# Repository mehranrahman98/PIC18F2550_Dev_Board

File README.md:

# PIC18F2550 Development Board
KiCAD PCB Design of PIC18F2550 development board. Similar to Arduino functionality.

## PCB

## Schematic

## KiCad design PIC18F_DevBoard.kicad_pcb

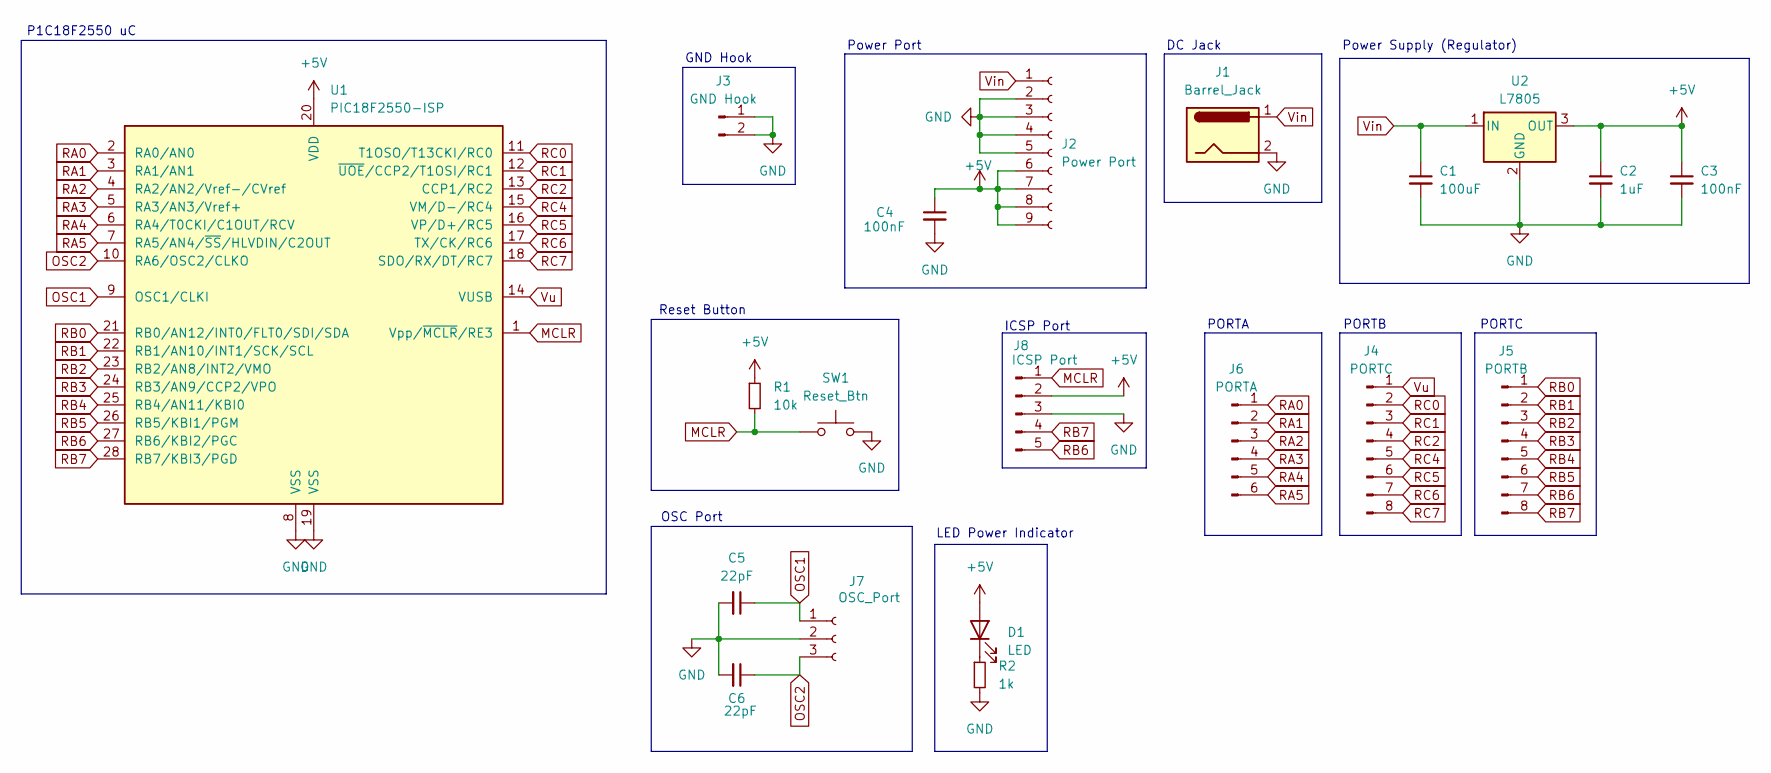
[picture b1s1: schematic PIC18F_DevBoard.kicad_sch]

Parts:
C1: 100uF; CP_Radial_D4.0mm_P2.00mm
C2: 1uF; CP_Radial_D4.0mm_P1.50mm
C3, C4: 100nF; C_Disc_D3.0mm_W1.6mm_P2.50mm
C5, C6: 22pF; C_Disc_D3.0mm_W1.6mm_P2.50mm
D1: LED; LED_D3.0mm
J1: Barrel_Jack; BarrelJack_Horizontal
J2: Power Port; PinSocket_1x09_P2.54mm_Vertical
J3: GND Hook; PinHeader_1x02_P2.54mm_Vertical
J4: PORTC; PinSocket_1x08_P2.54mm_Vertical
J5: PORTB; PinSocket_1x08_P2.54mm_Vertical
J6: PORTA; PinSocket_1x06_P2.54mm_Vertical
J7: OSC_Port; PinSocket_1x03_P2.54mm_Vertical
J8: ICSP Port; PinSocket_1x05_P2.54mm_Vertical
R1: 10k; R_Axial_DIN0204_L3.6mm_D1.6mm_P5.08mm_Horizontal
R2: 1k; R_Axial_DIN0204_L3.6mm_D1.6mm_P5.08mm_Horizontal
SW1: Reset_Btn; SW_PUSH_6mm
U1: PIC18F2550-ISP; DIP-28_W7.62mm
U2: L7805; TO-220-3_Horizontal_TabDown

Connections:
+5V: C2.1, C3.1, C4.1, D1.2 (A), J2.6, J2.7, J2.8, J2.9, J8.2, R1.1, U1.20 (VDD), U2.3 (OUT)
GND: C1.2, C2.2, C3.2, C4.2, C5.2, C6.2, J1.2, J2.2, J2.3, J2.4, J2.5, J3.1, J3.2, J7.2, J8.3, R2.2, SW1.2, U1.8 (VSS), U1.19 (VSS), U2.2 (GND)
MCLR: J8.1, R1.2, SW1.1, U1.1 (Vpp/~MCLR/RE3)
unnamed: D1.1 (K), R2.1
OSC1: C5.1, J7.1, U1.9 (OSC1/CLKI)
OSC2: C6.1, J7.3, U1.10 (RA6/OSC2/CLKO)
RA0: J6.1, U1.2 (RA0/AN0)
RA1: J6.2, U1.3 (RA1/AN1)
RA2: J6.3, U1.4 (RA2/AN2/Vref-/CVref)
RA3: J6.4, U1.5 (RA3/AN3/Vref+)
RA4: J6.5, U1.6 (RA4/T0CKI/C1OUT/RCV)
RA5: J6.6, U1.7 (RA5/AN4/~SS/HLVDIN/C2OUT)
RB0: J5.1, U1.21 (RB0/AN12/INT0/FLT0/SDI/SDA)
RB1: J5.2, U1.22 (RB1/AN10/INT1/SCK/SCL)
RB2: J5.3, U1.23 (RB2/AN8/INT2/VMO)
RB3: J5.4, U1.24 (RB3/AN9/CCP2/VPO)
RB4: J5.5, U1.25 (RB4/AN11/KBI0)
RB5: J5.6, U1.26 (RB5/KBI1/PGM)
RB6: J5.7, J8.5, U1.27 (RB6/KBI2/PGC)
RB7: J5.8, J8.4, U1.28 (RB7/KBI3/PGD)
RC0: J4.2, U1.11 (T1OSO/T13CKI/RC0)
RC1: J4.3, U1.12 (~UOE/CCP2/T1OSI/RC1)
RC2: J4.4, U1.13 (CCP1/RC2)
RC4: J4.5, U1.15 (VM/D-/RC4)
RC5: J4.6, U1.16 (VP/D+/RC5)
RC6: J4.7, U1.17 (TX/CK/RC6)
RC7: J4.8, U1.18 (SDO/RX/DT/RC7)
Vin: C1.1, J1.1, J2.1, U2.1 (IN)
Vu: J4.1, U1.14 (VUSB)

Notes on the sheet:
PORTB
Power Supply (Regulator)
GND Hook
PORTA
PORTC
Power Port
OSC Port
DC Jack
ICSP Port
P1C18F2550 uC
LED Power Indicator
Reset Button

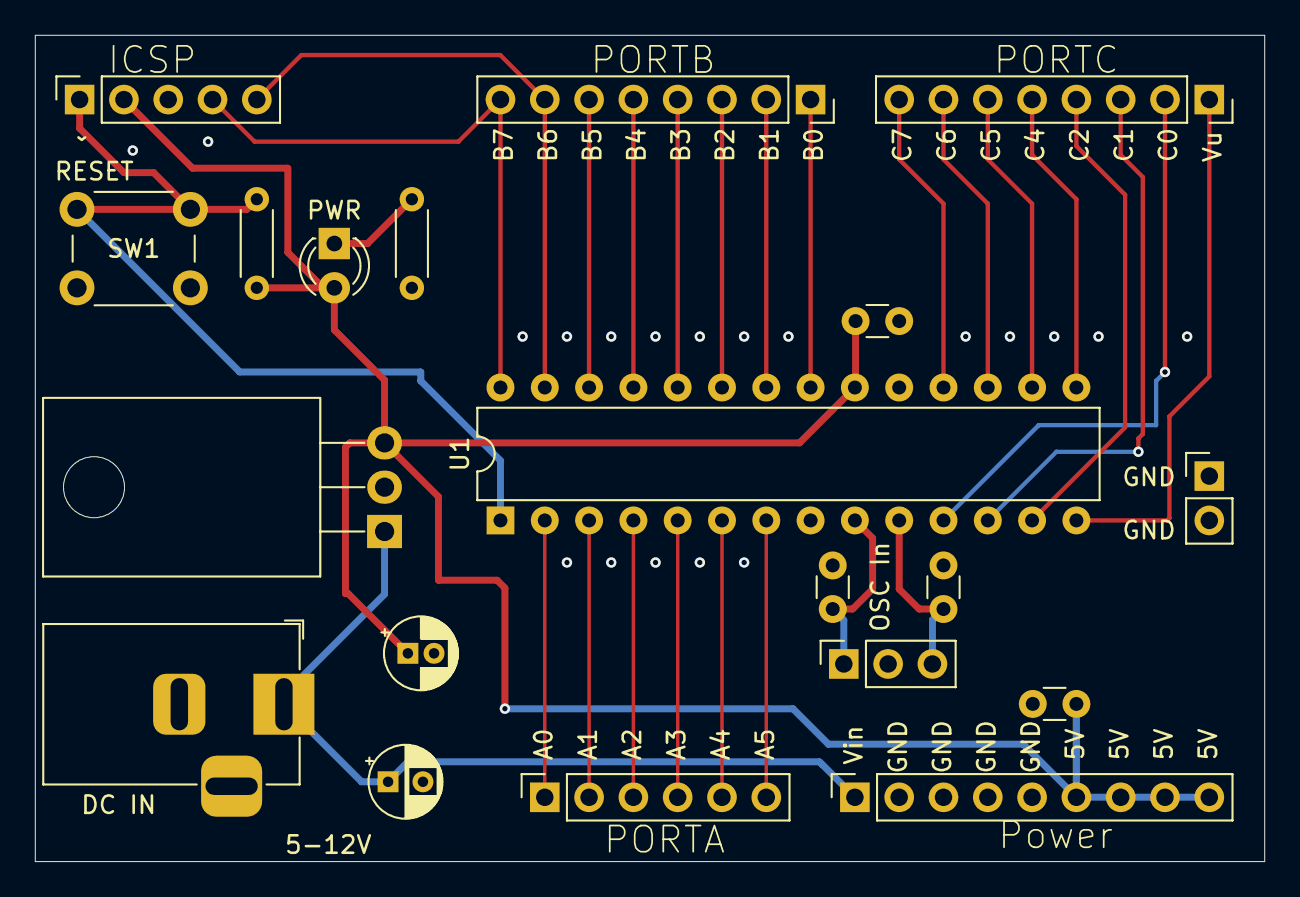
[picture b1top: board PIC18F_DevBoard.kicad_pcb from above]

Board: 2 copper layers, 70.5 x 47.4 mm, 20 parts (0 on the bottom side), 29 nets.
